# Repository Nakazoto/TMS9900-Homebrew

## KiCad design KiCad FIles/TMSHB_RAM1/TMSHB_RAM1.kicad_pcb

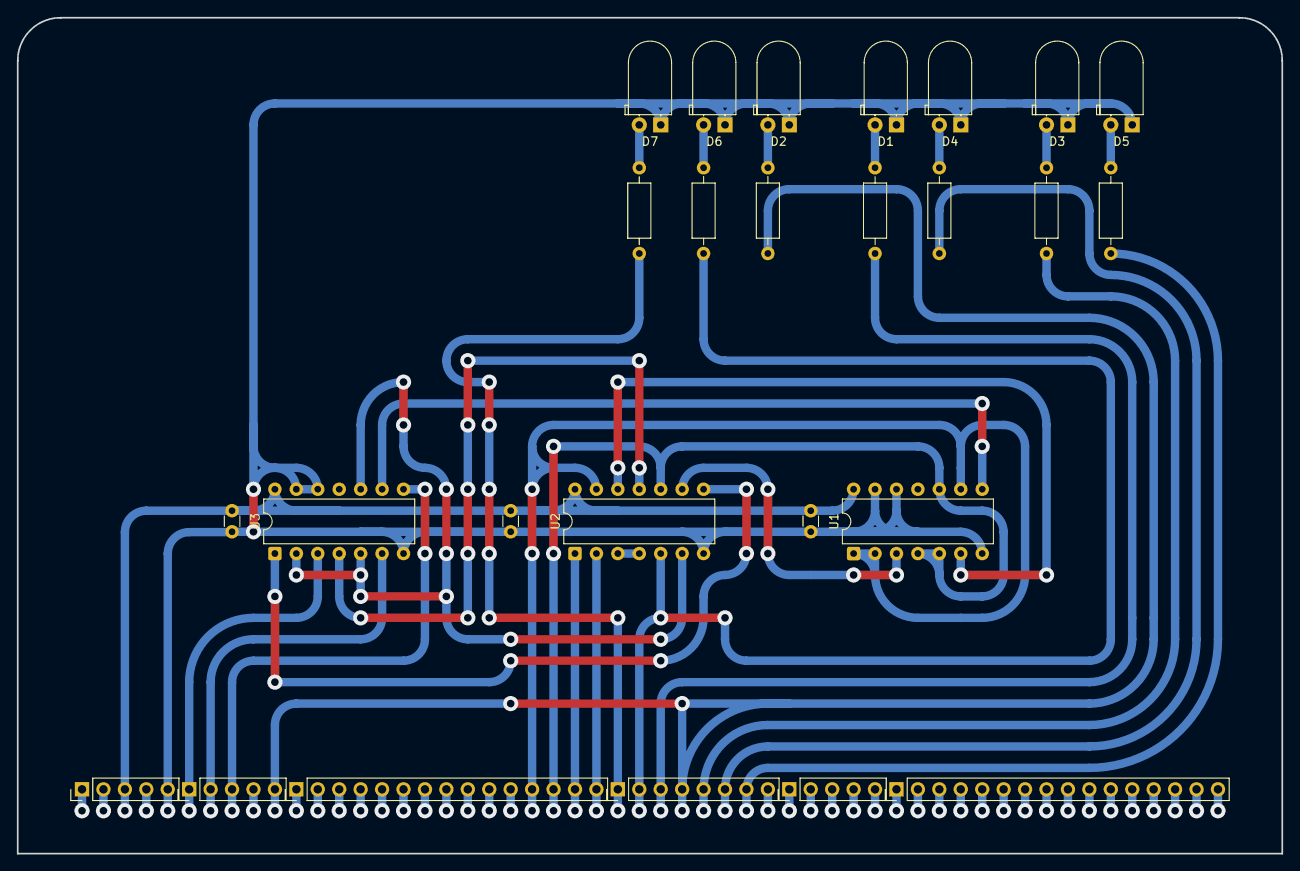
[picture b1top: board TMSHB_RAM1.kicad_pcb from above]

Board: 2 copper layers, 149.9 x 99.1 mm, 26 parts (0 on the bottom side), 30 nets.

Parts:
C1, C2, C3: C; C_Disc_D3.0mm_W1.6mm_P2.50mm
D1: READY; LED_D5.0mm_Horizontal_O1.27mm_Z3.0mm
D2: /WE; LED_D5.0mm_Horizontal_O1.27mm_Z3.0mm
D3: /HOLD; LED_D5.0mm_Horizontal_O1.27mm_Z3.0mm
D4: WAIT; LED_D5.0mm_Horizontal_O1.27mm_Z3.0mm
D5: HOLDA; LED_D5.0mm_Horizontal_O1.27mm_Z3.0mm
D6: /MEMIN; LED_D5.0mm_Horizontal_O1.27mm_Z3.0mm
D7: DBIN; LED_D5.0mm_Horizontal_O1.27mm_Z3.0mm
J1: Conn_01x08_Pin; PinHeader_1x08_P2.54mm_Vertical
J2: Conn_01x15_Pin; PinHeader_1x15_P2.54mm_Vertical
J3: Conn_01x16_Pin; PinHeader_1x16_P2.54mm_Vertical
J4, J5, J7: Conn_01x05_Pin; PinHeader_1x05_P2.54mm_Vertical
R13, R14, R15, R16, R17, R18, R19: 10k; R_Axial_DIN0207_L6.3mm_D2.5mm_P10.16mm_Horizontal
U1: 74LS00; DIP-14_W7.62mm
U2, U3: 74LS32; DIP-14_W7.62mm

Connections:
+5V: C1.1, C2.1, C3.1, J5.3, U1.14 (VCC), U2.14 (VCC), U3.14 (VCC)
/AD12: J2.12, U1.1, U1.2, U1.9, U2.13
/AD13: J2.13, U1.4, U1.5, U1.10, U2.10
/AD14: J2.14, U2.1
/AD15: J2.15, U2.2
/DBIN: J1.1, R19.1
/HOLDA: J1.7, R17.1
/READY: J1.3, R13.1
/WAIT: J1.6, R16.1
//HOLD: J1.5, R15.1
//MEMIN: J1.2, R18.1, U2.5
//WE: J1.4, J7.5, R14.1
GND: C1.2, C2.2, C3.2, D1.1 (K), D2.1 (K), D3.1 (K), D4.1 (K), D5.1 (K), D6.1 (K), D7.1 (K), J5.5, U1.7 (GND), U1.12, U1.13, U2.7 (GND), U3.7 (GND), U3.12, U3.13
unnamed: D1.2 (A), R13.2
unnamed: D2.2 (A), R14.2
unnamed: D3.2 (A), R15.2
unnamed: D4.2 (A), R16.2
unnamed: D5.2 (A), R17.2
unnamed: D6.2 (A), R18.2
unnamed: D7.2 (A), R19.2
unnamed: J7.1, U3.3
unnamed: J7.2, U3.6
unnamed: J7.3, U3.8
unnamed: U1.3, U2.9
unnamed: U1.6, U2.12
unnamed: U1.8, U3.9
unnamed: U2.3, U2.4
unnamed: U2.6, U3.2, U3.5, U3.10
unnamed: U2.8, U3.1
unnamed: U2.11, U3.4

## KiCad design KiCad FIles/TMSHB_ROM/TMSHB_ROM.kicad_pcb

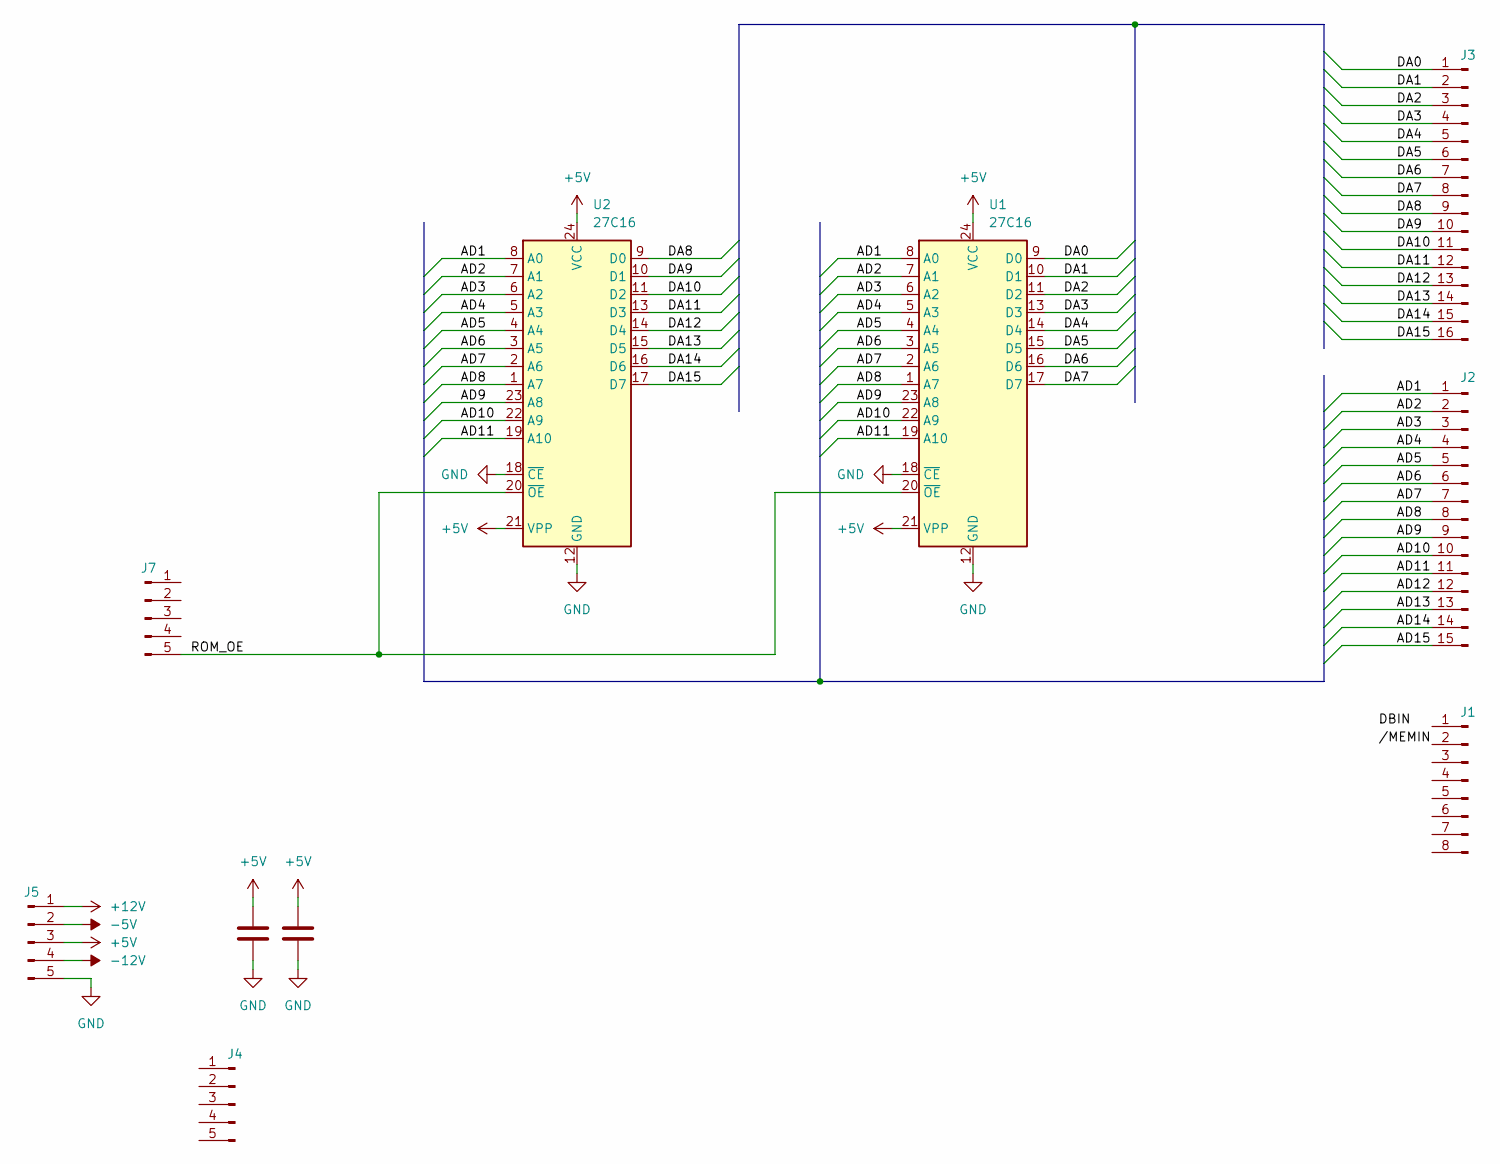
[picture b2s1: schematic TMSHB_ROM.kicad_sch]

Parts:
C1, C2: C; C_Disc_D3.0mm_W1.6mm_P2.50mm
J1: Conn_01x08_Pin; PinHeader_1x08_P2.54mm_Vertical
J2: Conn_01x15_Pin; PinHeader_1x15_P2.54mm_Vertical
J3: Conn_01x16_Pin; PinHeader_1x16_P2.54mm_Vertical
J4, J5, J7: Conn_01x05_Pin; PinHeader_1x05_P2.54mm_Vertical
U1, U2: 27C16; DIP-24_W15.24mm

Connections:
+5V: C1.1, C2.1, J5.3, U1.21 (VPP), U1.24 (VCC), U2.21 (VPP), U2.24 (VCC)
+12V: J5.1
-5V: J5.2
-12V: J5.4
/AD1: J2.1, U1.8 (A0), U2.8 (A0)
/AD2: J2.2, U1.7 (A1), U2.7 (A1)
/AD3: J2.3, U1.6 (A2), U2.6 (A2)
/AD4: J2.4, U1.5 (A3), U2.5 (A3)
/AD5: J2.5, U1.4 (A4), U2.4 (A4)
/AD6: J2.6, U1.3 (A5), U2.3 (A5)
/AD7: J2.7, U1.2 (A6), U2.2 (A6)
/AD8: J2.8, U1.1 (A7), U2.1 (A7)
/AD9: J2.9, U1.23 (A8), U2.23 (A8)
/AD10: J2.10, U1.22 (A9), U2.22 (A9)
/AD11: J2.11, U1.19 (A10), U2.19 (A10)
/AD12: J2.12
/AD13: J2.13
/AD14: J2.14
/AD15: J2.15
/DA0: J3.1, U1.9 (D0)
/DA1: J3.2, U1.10 (D1)
/DA2: J3.3, U1.11 (D2)
/DA3: J3.4, U1.13 (D3)
/DA4: J3.5, U1.14 (D4)
/DA5: J3.6, U1.15 (D5)
/DA6: J3.7, U1.16 (D6)
/DA7: J3.8, U1.17 (D7)
/DA8: J3.9, U2.9 (D0)
/DA9: J3.10, U2.10 (D1)
/DA10: J3.11, U2.11 (D2)
/DA11: J3.12, U2.13 (D3)
/DA12: J3.13, U2.14 (D4)
/DA13: J3.14, U2.15 (D5)
/DA14: J3.15, U2.16 (D6)
/DA15: J3.16, U2.17 (D7)
/ROM_OE: J7.5, U1.20 (~OE), U2.20 (~OE)
GND: C1.2, C2.2, J5.5, U1.12 (GND), U1.18 (~CE), U2.12 (GND), U2.18 (~CE)

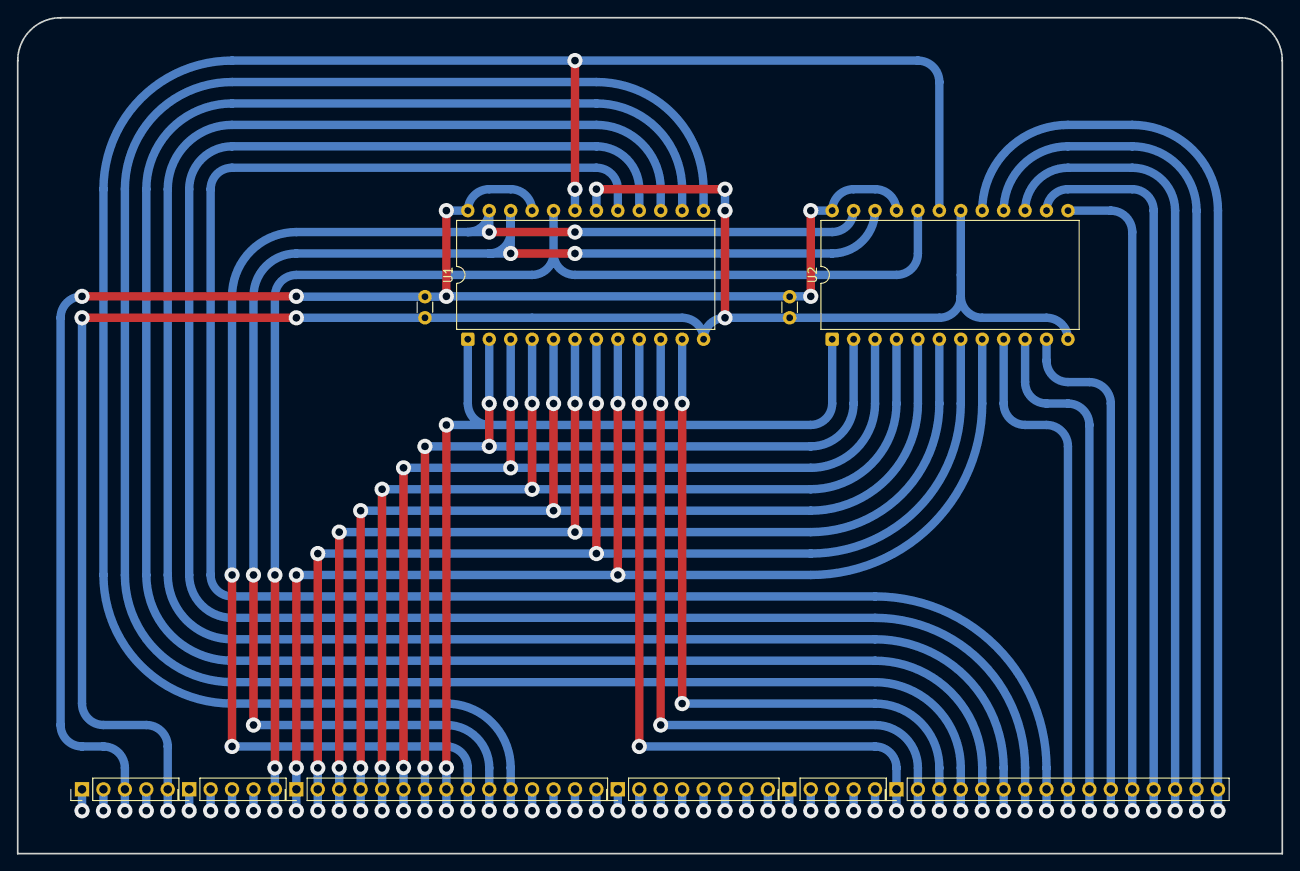
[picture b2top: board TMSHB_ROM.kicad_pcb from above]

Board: 2 copper layers, 149.9 x 99.1 mm, 10 parts (0 on the bottom side), 30 nets.

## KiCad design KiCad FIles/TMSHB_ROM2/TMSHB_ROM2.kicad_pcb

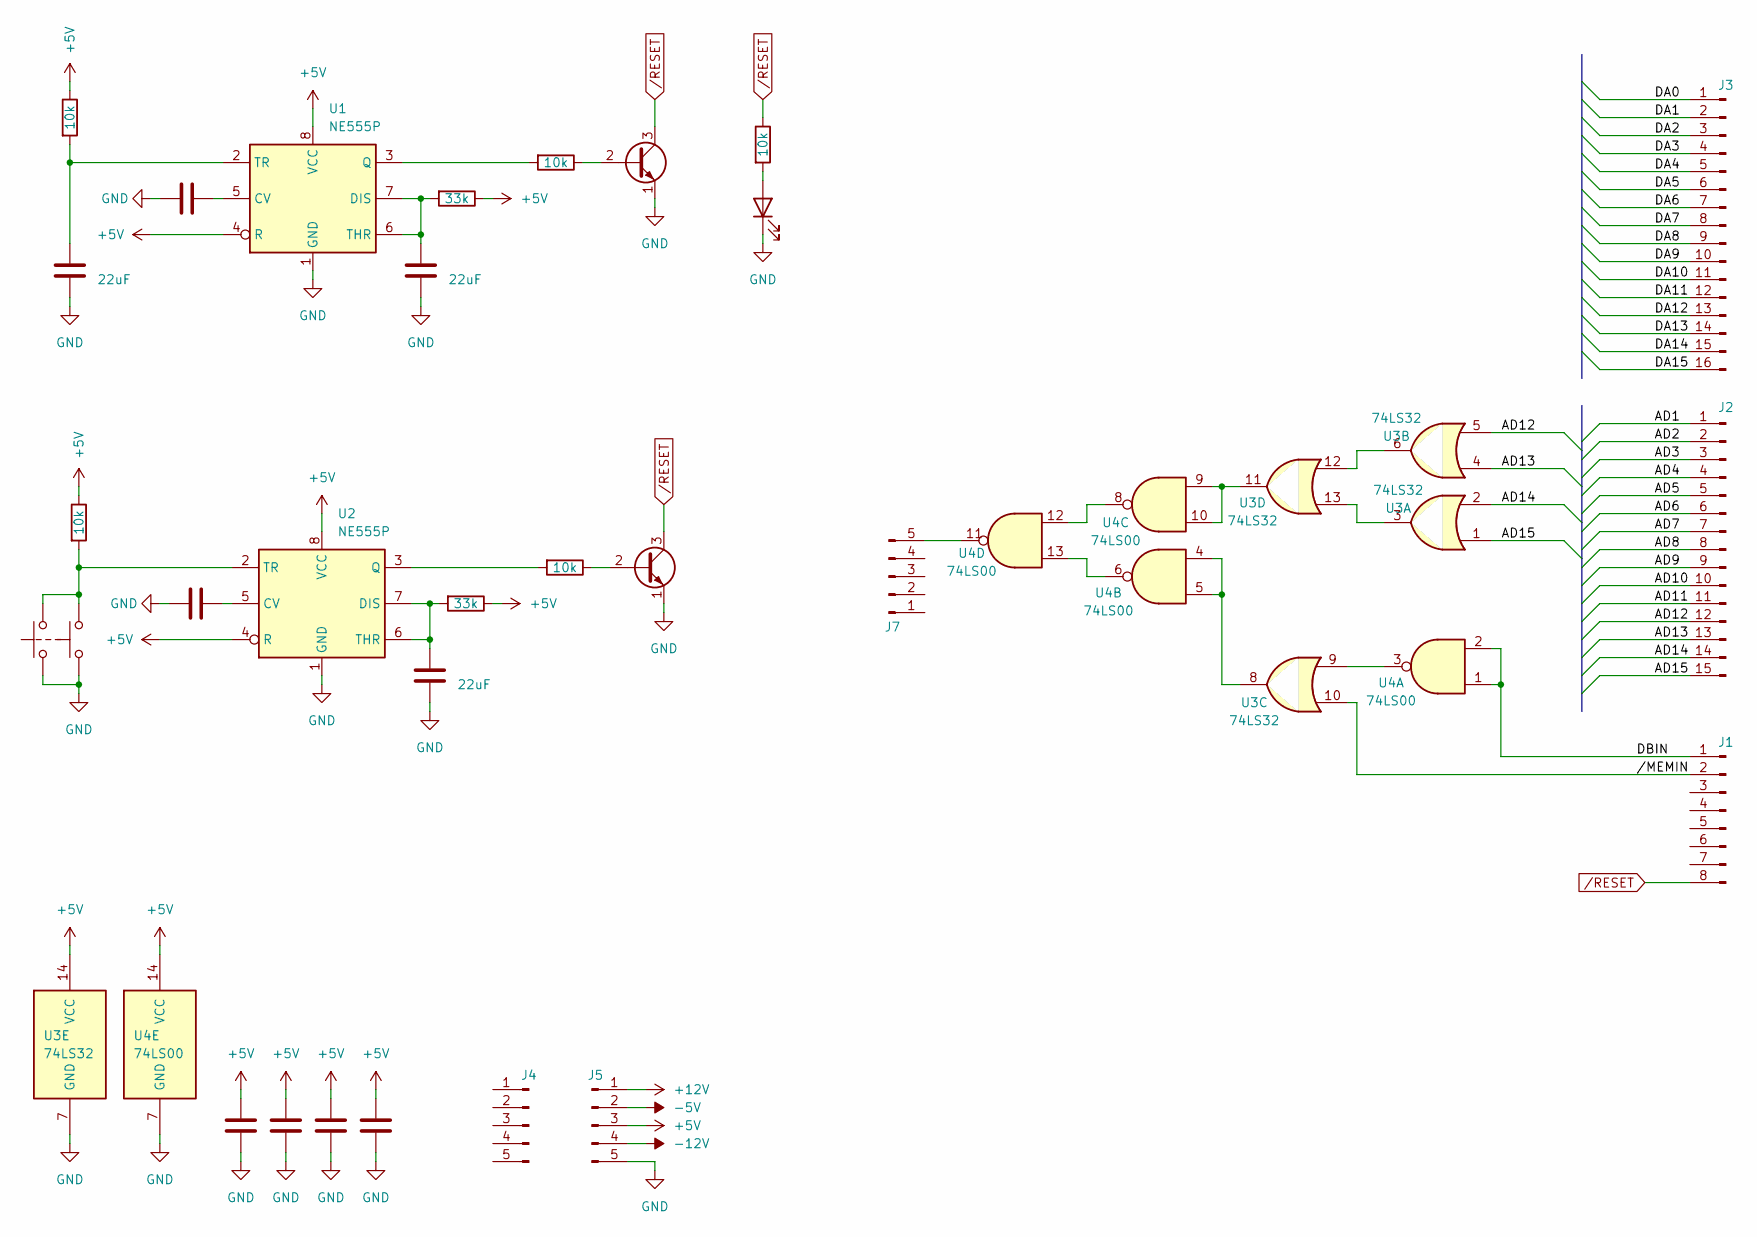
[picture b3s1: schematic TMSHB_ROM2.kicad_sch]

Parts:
C1, C2, C4, C6, C8, C9: C; C_Disc_D3.0mm_W1.6mm_P2.50mm
C3, C5, C7: 22uF; C_Radial_D5.0mm_H11.0mm_P2.00mm
D1: LED; LED_D5.0mm_Horizontal_O1.27mm_Z3.0mm
J1: Conn_01x08_Pin; PinHeader_1x08_P2.54mm_Vertical
J2: Conn_01x15_Pin; PinHeader_1x15_P2.54mm_Vertical
J3: Conn_01x16_Pin; PinHeader_1x16_P2.54mm_Vertical
J4, J5, J7: Conn_01x05_Pin; PinHeader_1x05_P2.54mm_Vertical
Q1, Q2: 2N3904; TO-92L_Wide
R7, R10: 33k; R_Axial_DIN0207_L6.3mm_D2.5mm_P10.16mm_Horizontal
R8, R9, R11, R12, R13: 10k; R_Axial_DIN0207_L6.3mm_D2.5mm_P10.16mm_Horizontal
SW1: SW_Double_Push; SW_Push_Double
U1, U2: NE555P; DIP-8_W7.62mm
U3: 74LS32; DIP-14_W7.62mm
U4: 74LS00; DIP-14_W7.62mm

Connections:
+5V: C1.1, C2.1, C6.1, C9.1, J5.3, R7.1, R8.1, R10.1, R11.1, U1.4 (R), U1.8 (VCC), U2.4 (R), U2.8 (VCC), U3.14 (VCC), U4.14 (VCC)
+12V: J5.1
-5V: J5.2
-12V: J5.4
/AD1: J2.1
/AD2: J2.2
/AD3: J2.3
/AD4: J2.4
/AD5: J2.5
/AD6: J2.6
/AD7: J2.7
/AD8: J2.8
/AD9: J2.9
/AD10: J2.10
/AD11: J2.11
/AD12: J2.12, U3.5
/AD13: J2.13, U3.4
/AD14: J2.14, U3.2
/AD15: J2.15, U3.1
/DA0: J3.1
/DA1: J3.2
/DA2: J3.3
/DA3: J3.4
/DA4: J3.5
/DA5: J3.6
/DA6: J3.7
/DA7: J3.8
/DA8: J3.9
/DA9: J3.10
/DA10: J3.11
/DA11: J3.12
/DA12: J3.13
/DA13: J3.14
/DA14: J3.15
/DA15: J3.16
/DBIN: J1.1, U4.1, U4.2
//MEMIN: J1.2, U3.10
GND: C1.2, C2.2, C3.2, C4.2, C5.2, C6.2, C7.2, C8.2, C9.2, D1.1 (K), J5.5, Q1.1 (E), Q2.1 (E), SW1.1, U1.1 (GND), U2.1 (GND), U3.7 (GND), U4.7 (GND)
unnamed: D1.2 (A), R13.2
unnamed: J7.5, U4.11
unnamed: Q1.2 (B), R9.1
unnamed: Q2.2 (B), R12.1
unnamed: C4.1, U1.5 (CV)
unnamed: C3.1, R7.2, U1.6 (THR), U1.7 (DIS)
unnamed: R9.2, U1.3 (Q)
unnamed: C5.1, R8.2, U1.2 (TR)
unnamed: C8.1, U2.5 (CV)
unnamed: C7.1, R10.2, U2.6 (THR), U2.7 (DIS)
unnamed: R12.2, U2.3 (Q)
unnamed: R11.2, SW1.2, U2.2 (TR)
unnamed: U3.8, U4.4, U4.5
unnamed: U3.9, U4.3
unnamed: U3.11, U4.9, U4.10
unnamed: U3.6, U3.12
unnamed: U3.3, U3.13
unnamed: U4.8, U4.12
unnamed: U4.6, U4.13
/RESET: J1.8, Q1.3 (C), Q2.3 (C), R13.1

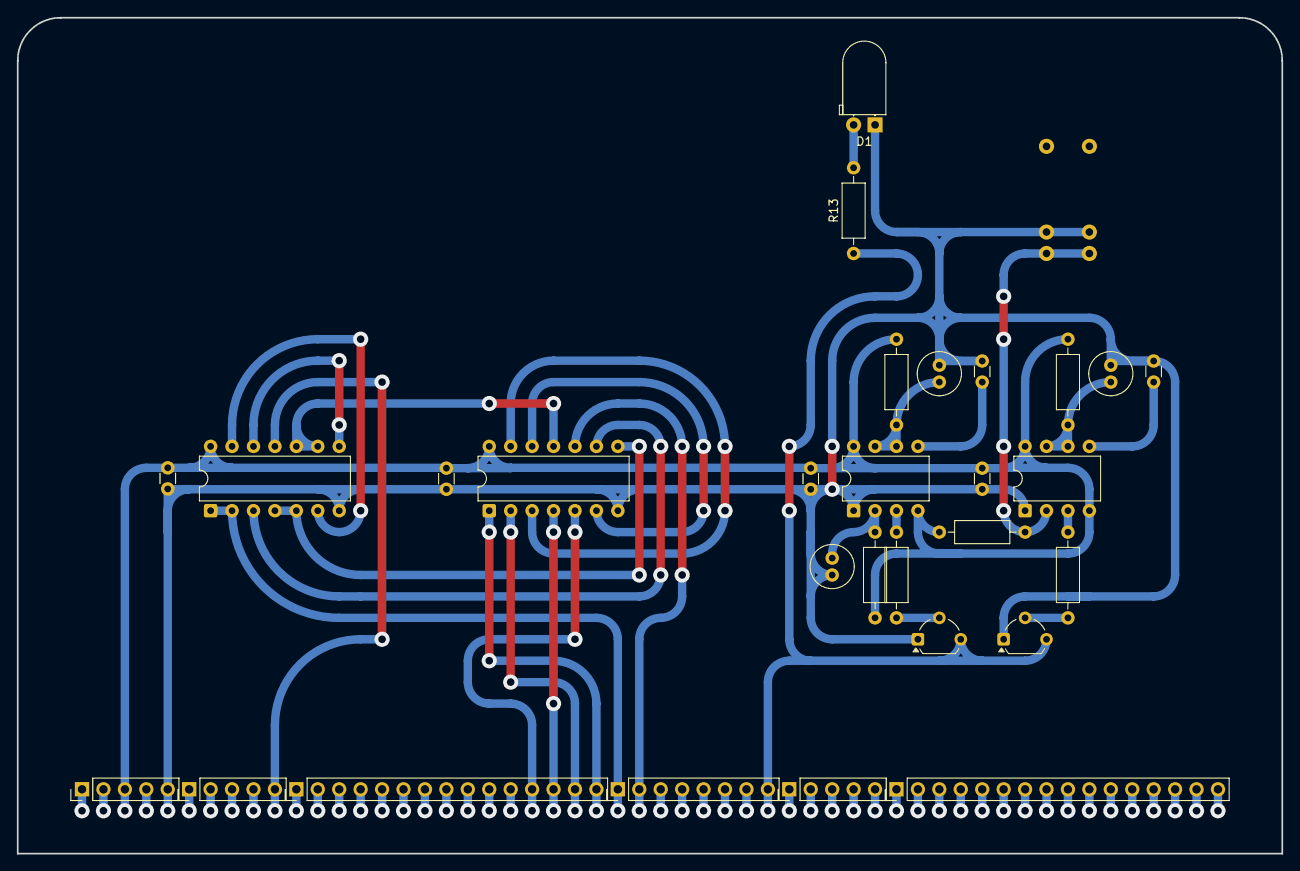
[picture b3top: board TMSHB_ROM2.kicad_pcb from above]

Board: 2 copper layers, 149.9 x 99.1 mm, 30 parts (0 on the bottom side), 28 nets.

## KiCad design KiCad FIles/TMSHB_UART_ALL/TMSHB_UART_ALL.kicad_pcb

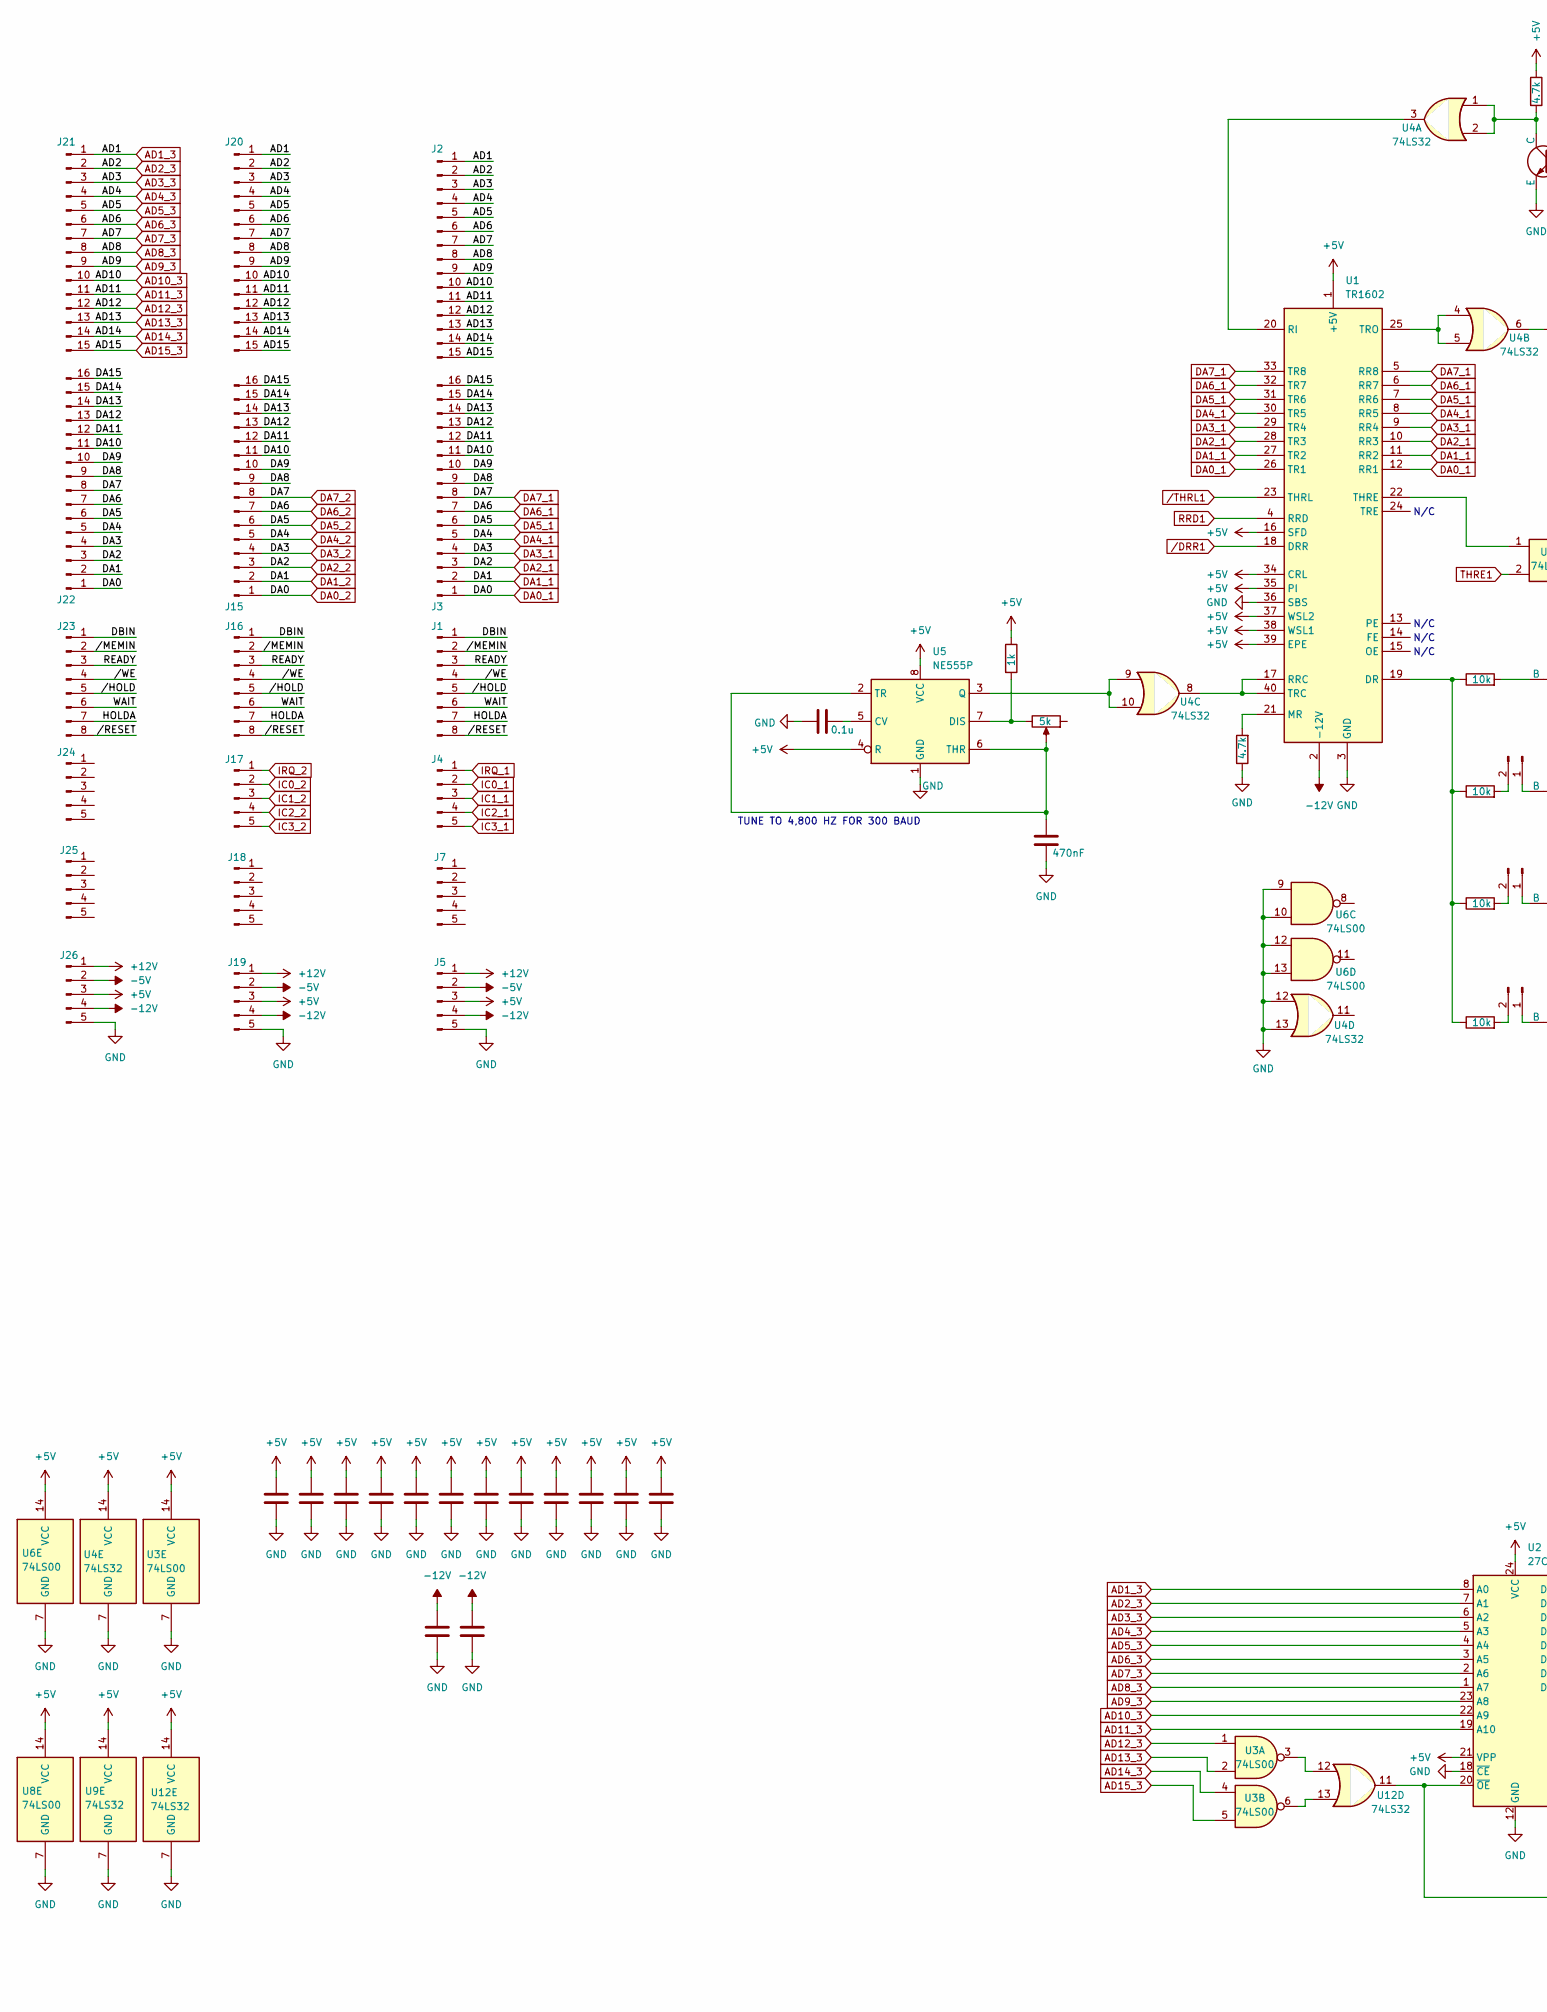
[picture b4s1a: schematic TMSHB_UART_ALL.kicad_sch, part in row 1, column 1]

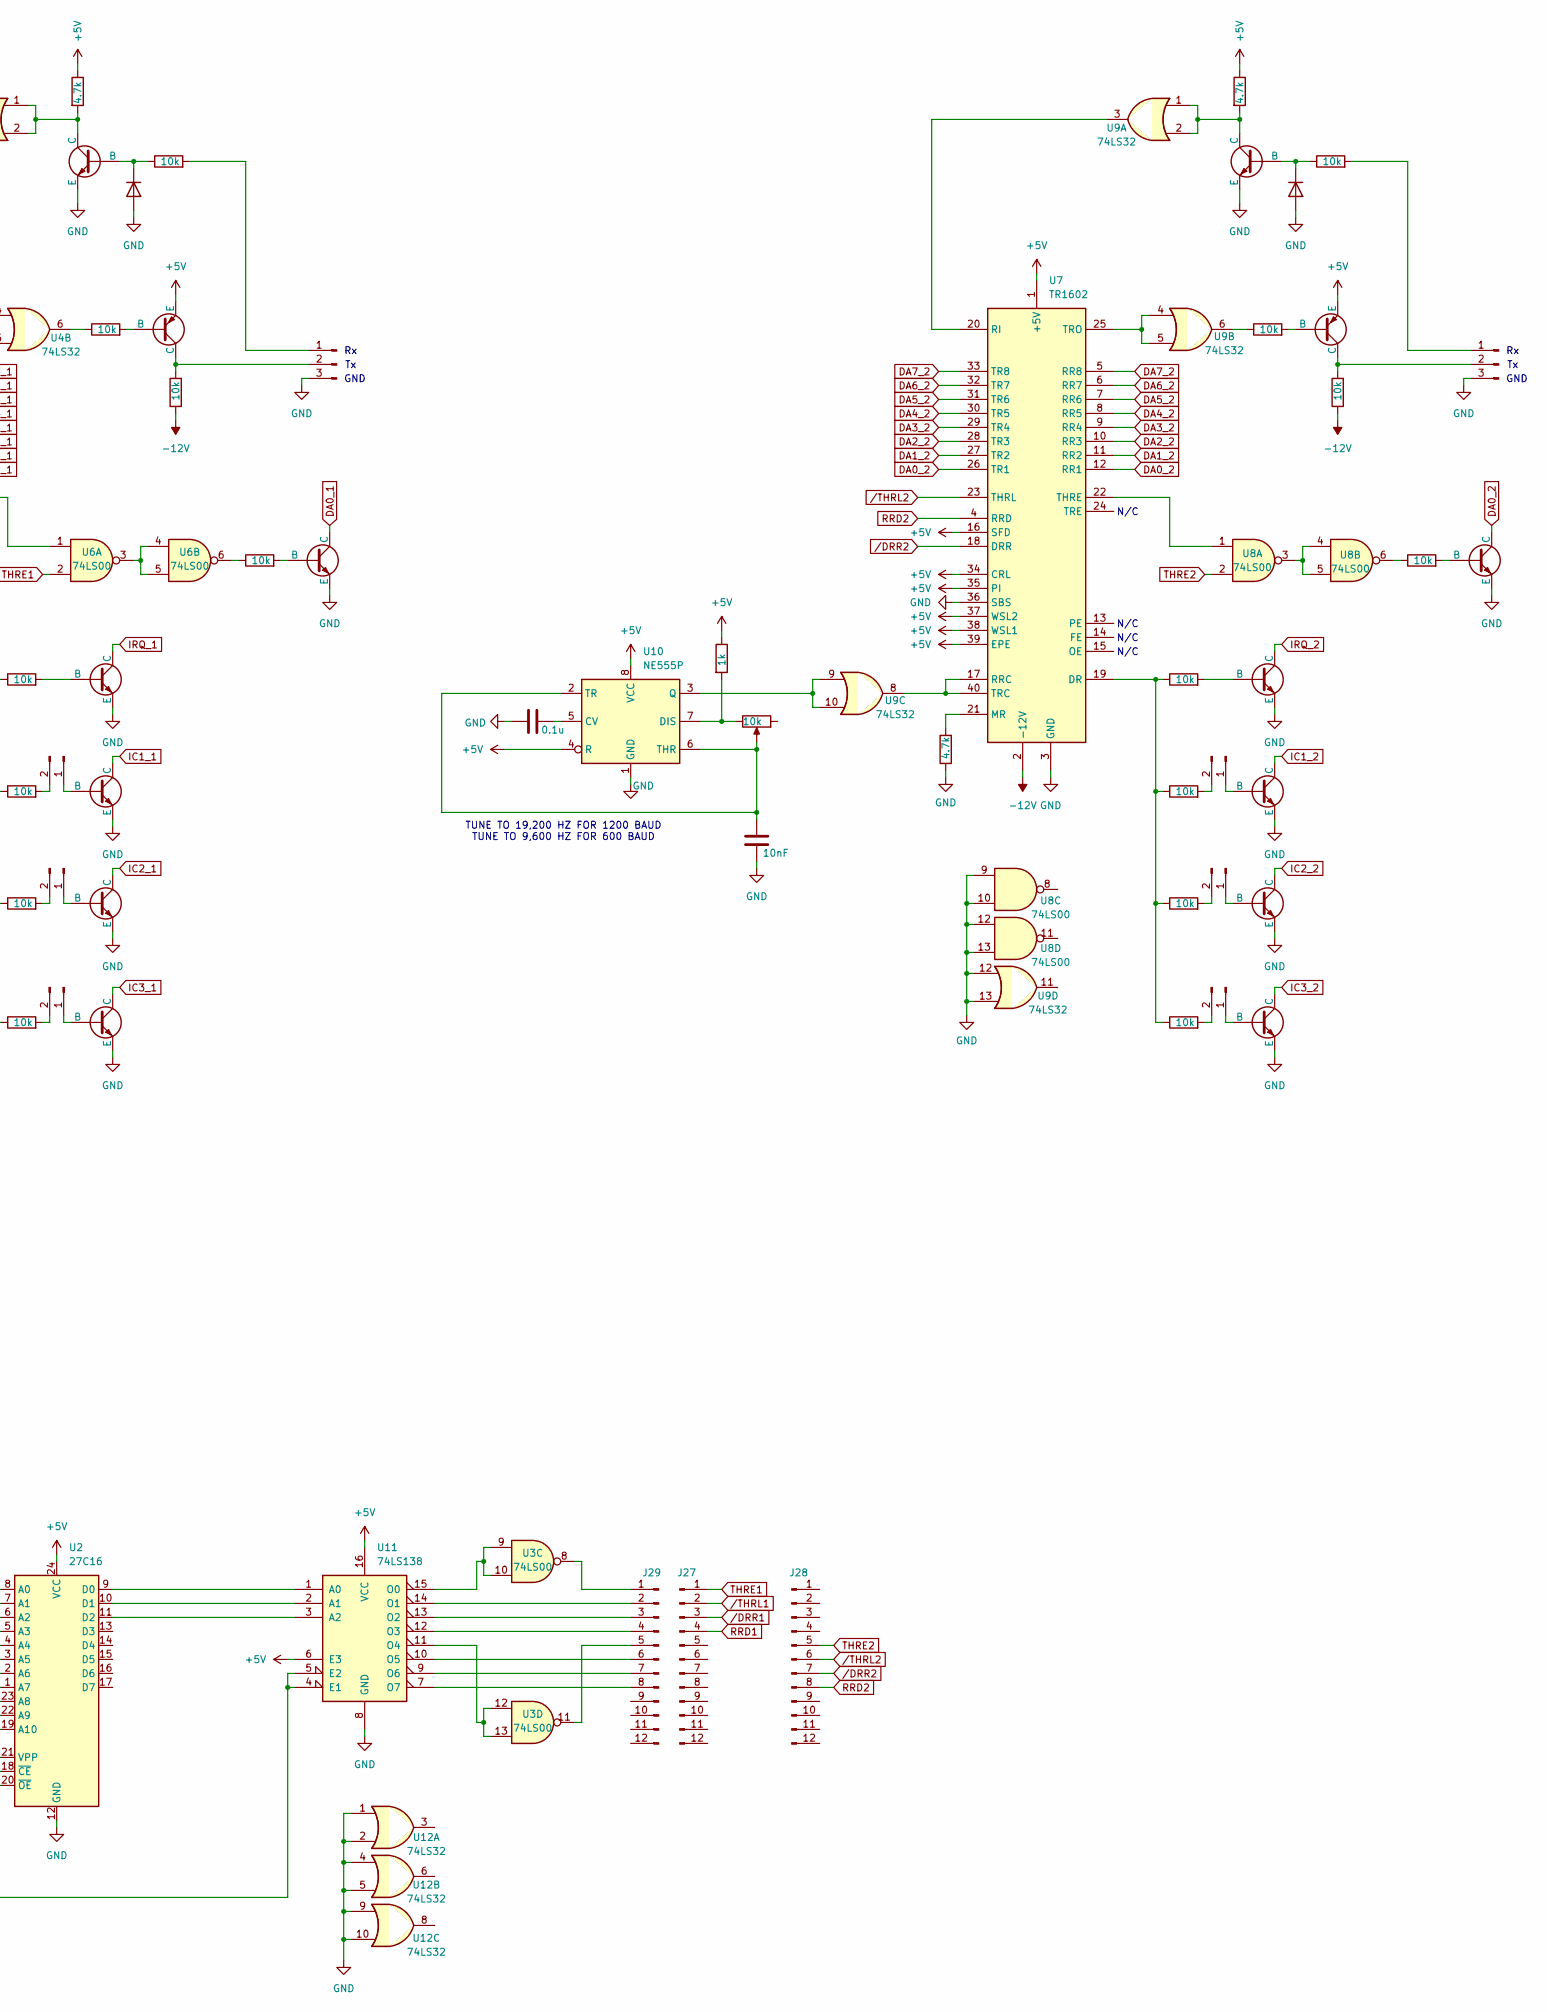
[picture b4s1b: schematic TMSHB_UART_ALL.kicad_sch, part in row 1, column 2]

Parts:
C1, C2, C3, C6, C9, C10, C11, C12, C13, C14, C15, C16, C17, C18: C; C_Disc_D3.0mm_W1.6mm_P2.50mm
C4: 470nF; C_Disc_D3.0mm_W1.6mm_P2.50mm
C5, C7: 0.1u; C_Disc_D3.0mm_W1.6mm_P2.50mm
C8: 10nF; C_Disc_D3.0mm_W1.6mm_P2.50mm
D1, D2: D; D_DO-34_SOD68_P7.62mm_Horizontal
J1, J16, J23: Conn_01x08_Pin; PinHeader_1x08_P2.54mm_Vertical
J2, J20, J21: Conn_01x15_Pin; PinHeader_1x15_P2.54mm_Vertical
J3, J15, J22: Conn_01x16_Pin; PinHeader_1x16_P2.54mm_Vertical
J4, J5, J7, J17, J18, J19, J24, J25, J26: Conn_01x05_Pin; PinHeader_1x05_P2.54mm_Vertical
J6, J8: Conn_01x03_Pin; PinHeader_1x03_P2.54mm_Vertical
J9, J10, J11, J12, J13, J14: Conn_01x02_Pin; PinHeader_1x02_P2.54mm_Vertical
J27, J28, J29: Conn_01x12_Pin; PinSocket_1x12_P2.54mm_Vertical
Q1, Q3, Q4, Q5, Q6, Q7, Q8, Q9, Q10, Q11, Q12, Q13: NPN; TO-92_Inline_Wide
Q2, Q14: PNP; TO-92_Inline_Wide
R3, R11, R16, R22: 4.7k; R_Axial_DIN0207_L6.3mm_D2.5mm_P10.16mm_Horizontal
R4, R26: 1k; R_Axial_DIN0207_L6.3mm_D2.5mm_P10.16mm_Horizontal
R5, R6, R7, R10, R12, R13, R14, R15, R17, R18, R19, R20, R21, R23, R24, R25: 10k; R_Axial_DIN0207_L6.3mm_D2.5mm_P10.16mm_Horizontal
RV1: 5k; Potentiometer_Bourns_3296W_Vertical
RV2: 10k; Potentiometer_Bourns_3296W_Vertical
U1, U7: TR1602; DIP-40_W15.24mm
U2: 27C16; DIP-24_W15.24mm
U3, U6, U8: 74LS00; DIP-14_W7.62mm
U4, U9, U12: 74LS32; DIP-14_W7.62mm
U5, U10: NE555P; DIP-8_W7.62mm
U11: 74LS138; DIP-16_W7.62mm

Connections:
+5V: C1.1, C2.1, C3.1, C6.1, C9.1, C10.1, C11.1, C12.1, C13.1, C14.1, C15.1, C16.1, J5.3, J19.3, J26.3, Q2.3 (E), Q14.3 (E), R4.1, R11.1, R22.1, R26.1, U1.1 (+5V), U1.16 (SFD), U1.34 (CRL), U1.35 (PI), U1.37 (WSL2), U1.38 (WSL1), U1.39 (EPE), U2.21 (VPP), U2.24 (VCC), U3.14 (VCC), U4.14 (VCC), U5.4 (R), U5.8 (VCC), U6.14 (VCC), U7.1 (+5V), U7.16 (SFD), U7.34 (CRL), U7.35 (PI), U7.37 (WSL2), U7.38 (WSL1), U7.39 (EPE), U8.14 (VCC), U9.14 (VCC), U10.4 (R), U10.8 (VCC), U11.6 (E3), U11.16 (VCC), U12.14 (VCC)
+12V: J5.1, J19.1, J26.1
-5V: J5.2, J19.2, J26.2
-12V: C17.1, C18.1, J5.4, J19.4, J26.4, R7.1, R25.1, U1.2 (-12V), U7.2 (-12V)
/DA8: J3.9, J15.9, J22.9
/DA9: J3.10, J15.10, J22.10
/DA10: J3.11, J15.11, J22.11
/DA11: J3.12, J15.12, J22.12
/DA12: J3.13, J15.13, J22.13
/DA13: J3.14, J15.14, J22.14
/DA14: J3.15, J15.15, J22.15
/DA15: J3.16, J15.16, J22.16
/DBIN: J1.1, J16.1, J23.1
/HOLDA: J1.7, J16.7, J23.7
/READY: J1.3, J16.3, J23.3
/WAIT: J1.6, J16.6, J23.6
//HOLD: J1.5, J16.5, J23.5
//MEMIN: J1.2, J16.2, J23.2
//RESET: J1.8, J16.8, J23.8
//WE: J1.4, J16.4, J23.4
AD1_3: J2.1, J20.1, J21.1, U2.8 (A0)
AD2_3: J2.2, J20.2, J21.2, U2.7 (A1)
AD3_3: J2.3, J20.3, J21.3, U2.6 (A2)
AD4_3: J2.4, J20.4, J21.4, U2.5 (A3)
AD5_3: J2.5, J20.5, J21.5, U2.4 (A4)
AD6_3: J2.6, J20.6, J21.6, U2.3 (A5)
AD7_3: J2.7, J20.7, J21.7, U2.2 (A6)
AD8_3: J2.8, J20.8, J21.8, U2.1 (A7)
AD9_3: J2.9, J20.9, J21.9, U2.23 (A8)
AD10_3: J2.10, J20.10, J21.10, U2.22 (A9)
AD11_3: J2.11, J20.11, J21.11, U2.19 (A10)
AD12_3: J2.12, J20.12, J21.12, U3.1
AD13_3: J2.13, J20.13, J21.13, U3.2
AD14_3: J2.14, J20.14, J21.14, U3.4
AD15_3: J2.15, J20.15, J21.15, U3.5
DA0_1: J3.1, J15.1, J22.1, Q1.1 (C), Q12.1 (C), U1.12 (RR1), U1.26 (TR1), U7.12 (RR1), U7.26 (TR1)
DA1_1: J3.2, J15.2, J22.2, U1.11 (RR2), U1.27 (TR2), U7.11 (RR2), U7.27 (TR2)
DA2_1: J3.3, J15.3, J22.3, U1.10 (RR3), U1.28 (TR3), U7.10 (RR3), U7.28 (TR3)
DA3_1: J3.4, J15.4, J22.4, U1.9 (RR4), U1.29 (TR4), U7.9 (RR4), U7.29 (TR4)
DA4_1: J3.5, J15.5, J22.5, U1.8 (RR5), U1.30 (TR5), U7.8 (RR5), U7.30 (TR5)
DA5_1: J3.6, J15.6, J22.6, U1.7 (RR6), U1.31 (TR6), U7.7 (RR6), U7.31 (TR6)
DA6_1: J3.7, J15.7, J22.7, U1.6 (RR7), U1.32 (TR7), U7.6 (RR7), U7.32 (TR7)
DA7_1: J3.8, J15.8, J22.8, U1.5 (RR8), U1.33 (TR8), U7.5 (RR8), U7.33 (TR8)
GND: C1.2, C2.2, C3.2, C4.2, C5.1, C6.2, C7.1, C8.2, C9.2, C10.2, C11.2, C12.2, C13.2, C14.2, C15.2, C16.2, C17.2, C18.2, D1.2 (A), D2.2 (A), J5.5, J6.3, J8.3, J19.5, J26.5, Q1.3 (E), Q3.3 (E), Q4.3 (E), Q5.3 (E), Q6.3 (E), Q7.3 (E), Q8.3 (E), Q9.3 (E), Q10.3 (E), Q11.3 (E), Q12.3 (E), Q13.3 (E), R3.1, R16.1, U1.3 (GND), U1.36 (SBS), U2.12 (GND), U2.18 (~CE), U3.7 (GND), U4.7 (GND), U4.12, U4.13, U5.1 (GND), U6.7 (GND), U6.9, U6.10, U6.12, U6.13, U7.3 (GND), U7.36 (SBS), U8.7 (GND), U8.9, U8.10, U8.12, U8.13, U9.7 (GND), U9.12, U9.13, U10.1 (GND), U11.8 (GND), U12.1, U12.2, U12.4, U12.5, U12.7 (GND), U12.9, U12.10
IC0_1: J4.2
IC0_2: J17.2
IC1_1: J4.3, Q5.1 (C)
IC1_2: J17.3, Q9.1 (C)
IC2_1: J4.4, Q6.1 (C)
IC2_2: J17.4, Q10.1 (C)
IC3_1: J4.5, Q7.1 (C)
IC3_2: J17.5, Q11.1 (C)
IRQ_1: J4.1, Q4.1 (C)
IRQ_2: J17.1, Q8.1 (C)
unnamed: D1.1 (K), Q3.2 (B), R10.1
unnamed: D2.1 (K), Q13.2 (B), R24.1
unnamed: J6.1, R10.2
unnamed: J6.2, Q2.1 (C), R7.2
unnamed: J8.1, R24.2
unnamed: J8.2, Q14.1 (C), R25.2
unnamed: J9.1, Q7.2 (B)
unnamed: J9.2, R15.2
unnamed: J10.1, Q6.2 (B)
unnamed: J10.2, R14.2
unnamed: J11.1, Q5.2 (B)
unnamed: J11.2, R13.2
unnamed: J12.1, Q9.2 (B)
unnamed: J12.2, R18.2
unnamed: J13.1, Q10.2 (B)
unnamed: J13.2, R19.2
unnamed: J14.1, Q11.2 (B)
unnamed: J14.2, R20.2
unnamed: J29.1, U3.8
unnamed: J29.2, U11.14 (O1)
unnamed: J29.3, U11.13 (O2)
unnamed: J29.4, U11.12 (O3)
unnamed: J29.5, U3.11
unnamed: J29.6, U11.10 (O5)
unnamed: J29.7, U11.9 (O6)
unnamed: J29.8, U11.7 (O7)
unnamed: Q1.2 (B), R5.2
unnamed: Q2.2 (B), R6.2
unnamed: Q3.1 (C), R11.2, U4.1, U4.2
unnamed: Q4.2 (B), R12.2
unnamed: Q8.2 (B), R17.2
unnamed: Q12.2 (B), R21.2
unnamed: Q13.1 (C), R22.2, U9.1, U9.2
unnamed: Q14.2 (B), R23.2
unnamed: R5.1, U6.6
unnamed: R6.1, U4.6
unnamed: R21.1, U8.6
unnamed: R23.1, U9.6
unnamed: R12.1, R13.1, R14.1, R15.1, U1.19 (DR)
unnamed: R3.2, U1.21 (MR)
unnamed: U1.20 (RI), U4.3
unnamed: U1.17 (RRC), U1.40 (TRC), U4.8
unnamed: U1.22 (THRE), U6.1
unnamed: U1.25 (TRO), U4.4, U4.5
unnamed: C5.2, U5.5 (CV)
unnamed: R4.2, RV1.3, U5.7 (DIS)
unnamed: U4.9, U4.10, U5.3 (Q)
unnamed: C4.1, RV1.2, U5.2 (TR), U5.6 (THR)
unnamed: U6.3, U6.4, U6.5
unnamed: R17.1, R18.1, R19.1, R20.1, U7.19 (DR)
unnamed: R16.2, U7.21 (MR)
unnamed: U7.20 (RI), U9.3
unnamed: U7.17 (RRC), U7.40 (TRC), U9.8
unnamed: U7.22 (THRE), U8.1
unnamed: U7.25 (TRO), U9.4, U9.5
unnamed: U8.3, U8.4, U8.5
unnamed: C7.2, U10.5 (CV)
unnamed: R26.2, RV2.3, U10.7 (DIS)
unnamed: U9.9, U9.10, U10.3 (Q)
unnamed: C8.1, RV2.2, U10.2 (TR), U10.6 (THR)
unnamed: U2.9 (D0), U11.1 (A0)
unnamed: U2.10 (D1), U11.2 (A1)
unnamed: U2.11 (D2), U11.3 (A2)
unnamed: U2.20 (~OE), U11.4 (E1), U11.5 (E2), U12.11
unnamed: U3.9, U3.10, U11.15 (O0)
unnamed: U3.12, U3.13, U11.11 (O4)
unnamed: U3.3, U12.12
unnamed: U3.6, U12.13
RRD1: J27.4, U1.4 (RRD)
RRD2: J28.8, U7.4 (RRD)
THRE1: J27.1, U6.2
THRE2: J28.5, U8.2
/DRR1: J27.3, U1.18 (DRR)
/DRR2: J28.7, U7.18 (DRR)
/THRL1: J27.2, U1.23 (THRL)
/THRL2: J28.6, U7.23 (THRL)

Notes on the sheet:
GND
TUNE TO 19,200 HZ FOR 1200 BAUD TUNE TO 9,600 HZ FOR 600 BAUD
N/C
TUNE TO 4,800 HZ FOR 300 BAUD

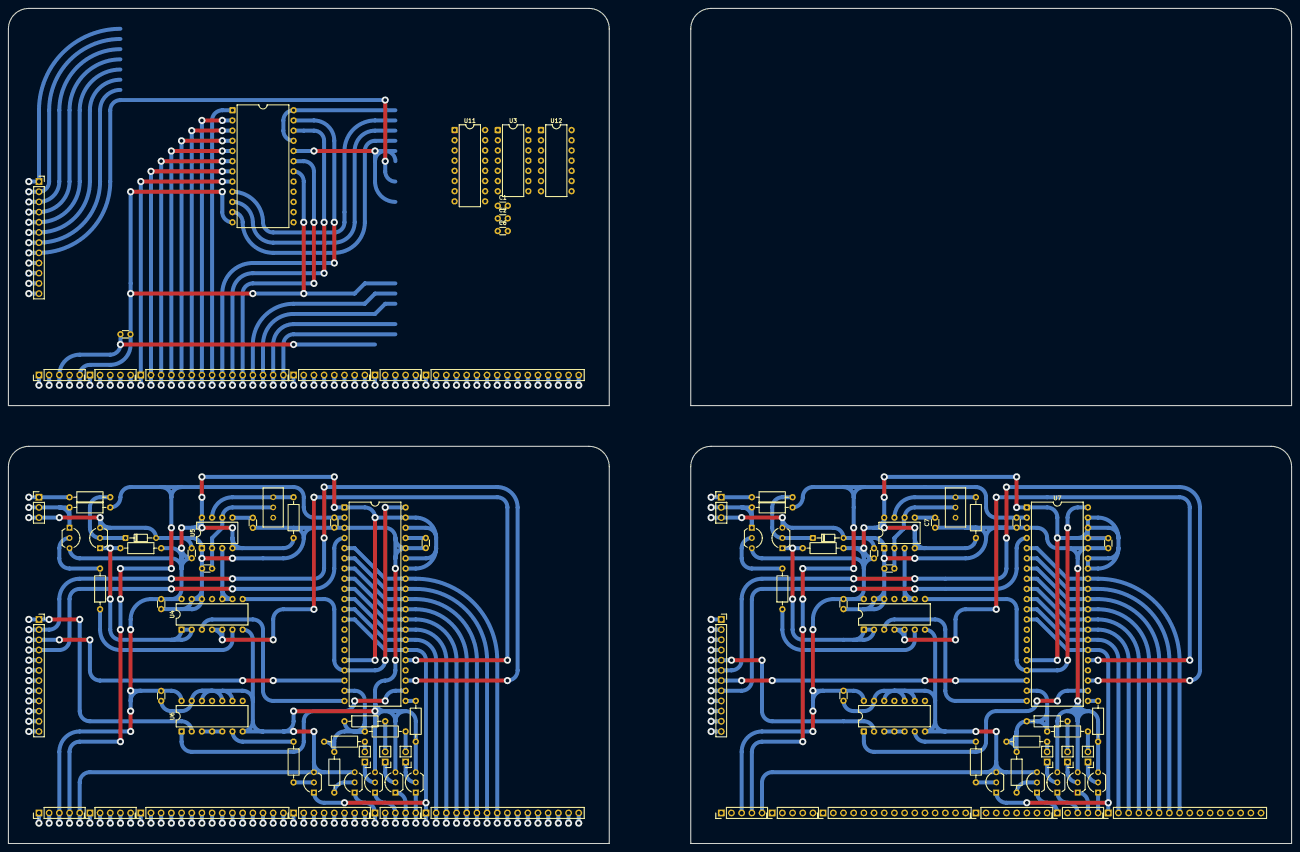
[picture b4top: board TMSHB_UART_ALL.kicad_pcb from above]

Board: 2 copper layers, 320.0 x 208.3 mm, 99 parts (0 on the bottom side), 128 nets.
